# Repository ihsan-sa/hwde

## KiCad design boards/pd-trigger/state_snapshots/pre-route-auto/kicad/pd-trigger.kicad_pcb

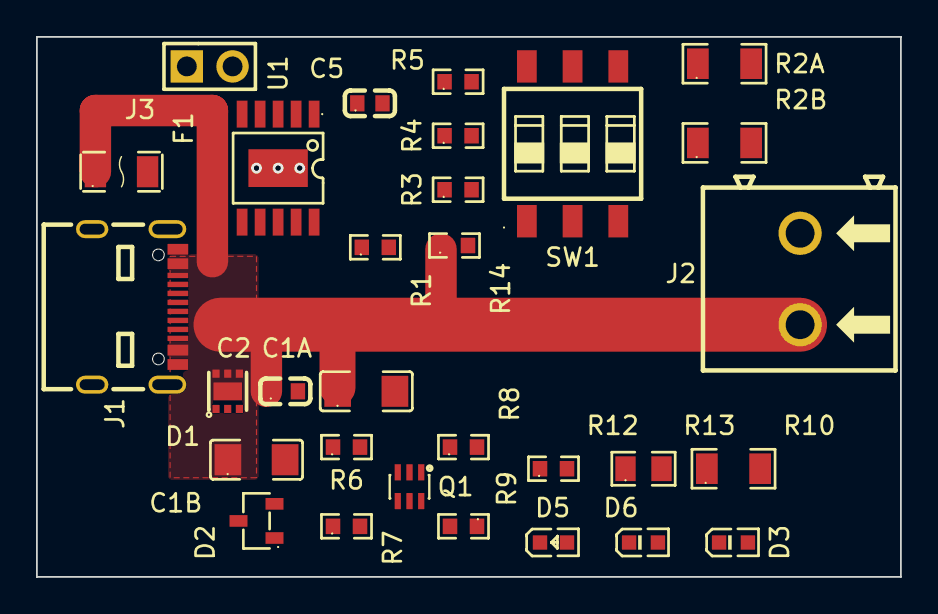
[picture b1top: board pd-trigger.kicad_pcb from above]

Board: 2 copper layers, 48.0 x 30.0 mm, 30 parts (0 on the bottom side), 21 nets.

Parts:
C1A, C1B: 10uF 50V X5R; C1206
C2: 100nF 50V X7R; C0603
C5: 1uF 50V X5R; C0603
D1: TVS2200 22V; WSON-6_L2.0-W2.0-P0.65-BL-EP
D2: BZX84C6V2; SOT-23-3_L2.9-W1.3-P1.90-LS2.4-BR
D3: LED YG PWR; LED0603-RD_GREEN
D5: LED RED 5V ONLY; LED0603-RD
D6: LED YG PROFILE OK; LED0603-RD_GREEN
F1: PPTC 1A 30V; F1206
J1: USB-C 16P 5A; USB-C-SMD_MC-311D
J2: SCREW 5.08 2P; CONN-TH_P5.08_KF128-5.08-2P
J3: HDR 1x2 AUX; HDR-TH_2P-P2.54-V-M-3
Q1: BC847BS; SOT-363-6_L2.2-W1.3-P0.65-LS2.1-BL
R1, R8: 10k; R0603
R2A, R2B: 510R; R1206
R3, R4, R5: 100k; R0603
R6: 6.8k; R0603
R7: 4.7k; R0603
R9: 47k; R0603
R10: 3.3k; R1206
R12: 1.5k; R0603
R13: 4.7k; R0805
R14: 0R; R0603
SW1: DIP-3; SW-SMD_6P-L7.6-W6.0-P2.54-LS9.3-BL
U1: CH224K; ESSOP-10_L4.9-W3.9-P1.0-LS6.0-TL-EP

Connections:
/BC12_DIS: U1.4, U1.5
/CC1: J1.A5, U1.7
/CC2: J1.B5, U1.6
/CFG1: R3.2, SW1.1, U1.9
/CFG2: R4.2, SW1.2, U1.2
/CFG3: R5.2, SW1.3, U1.3
/D3_A: D3.2, R10.2
/D5_A: D5.2, R12.2
/D6_A: D6.2, R13.2
/FB_B: Q1.5, R9.2
/FB_K: D5.1, Q1.3
/HV_B: Q1.2, R6.2, R7.1
/HV_OK: D6.1, Q1.6, R8.2, R9.1
/R2_MID: R2A.2, R2B.1
/VAUX: F1.2, J3.1
/VDD: C5.1, R2B.2, R3.1, R4.1, R5.1, U1.1
/VIND: D2.3, R1.1, R2A.1, R8.1, R10.1, R12.1, R13.1, R14.2
/VSENSE: R1.2, U1.8
/ZBIAS: D2.1, R6.1
GND: C1A.2, C1B.2, C2.2, C5.2, D1.1, D1.2, D1.3, D1.7, D3.1, J1.1, J1.2, J1.3, J1.4, J1.A1-B12, J1.B1-A12, J2.2, J3.2, Q1.1, Q1.4, R7.2, SW1.4, SW1.5, SW1.6, U1.11
VBUS: C1A.1, C1B.1, C2.1, D1.4, D1.5, D1.6, F1.1, J1.A4-B9, J1.B4-A9, J2.1, R14.1

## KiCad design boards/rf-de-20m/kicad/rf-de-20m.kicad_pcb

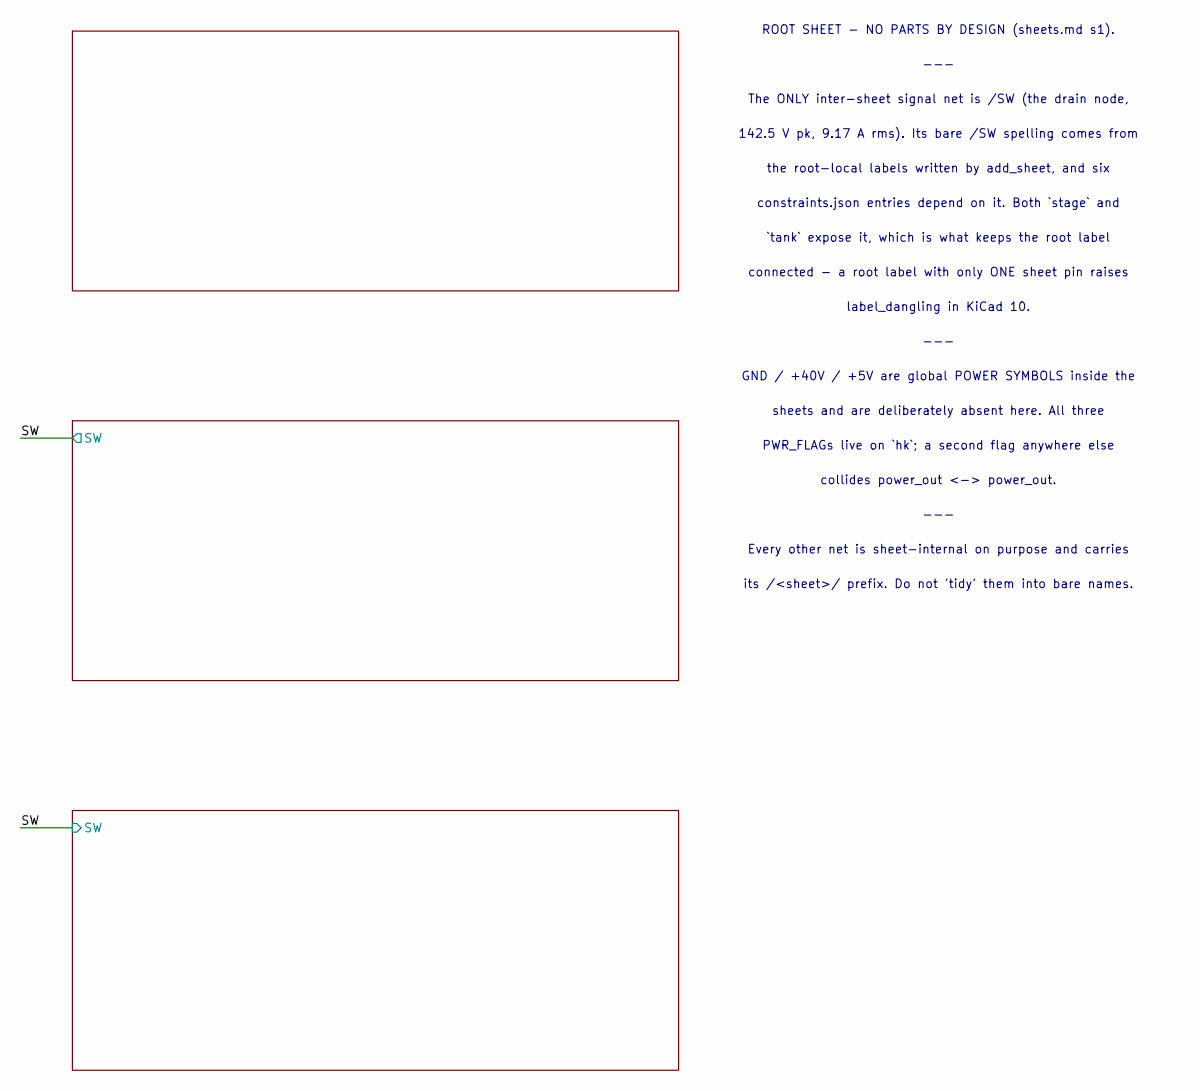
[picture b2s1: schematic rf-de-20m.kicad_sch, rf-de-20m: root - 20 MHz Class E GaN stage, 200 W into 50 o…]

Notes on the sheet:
ROOT SHEET - NO PARTS BY DESIGN (sheets.md s1).
---
The ONLY inter-sheet signal net is /SW (the drain node,
142.5 V pk, 9.17 A rms). Its bare /SW spelling comes from
the root-local labels written by add_sheet, and six
constraints.json entries depend on it. Both `stage` and
`tank` expose it, which is what keeps the root label
connected - a root label with only ONE sheet pin raises
label_dangling in KiCad 10.
GND / +40V / +5V are global POWER SYMBOLS inside the
sheets and are deliberately absent here. All three
PWR_FLAGs live on `hk`; a second flag anywhere else
collides power_out <-> power_out.
Every other net is sheet-internal on purpose and carries
its /<sheet>/ prefix. Do not 'tidy' them into bare names.

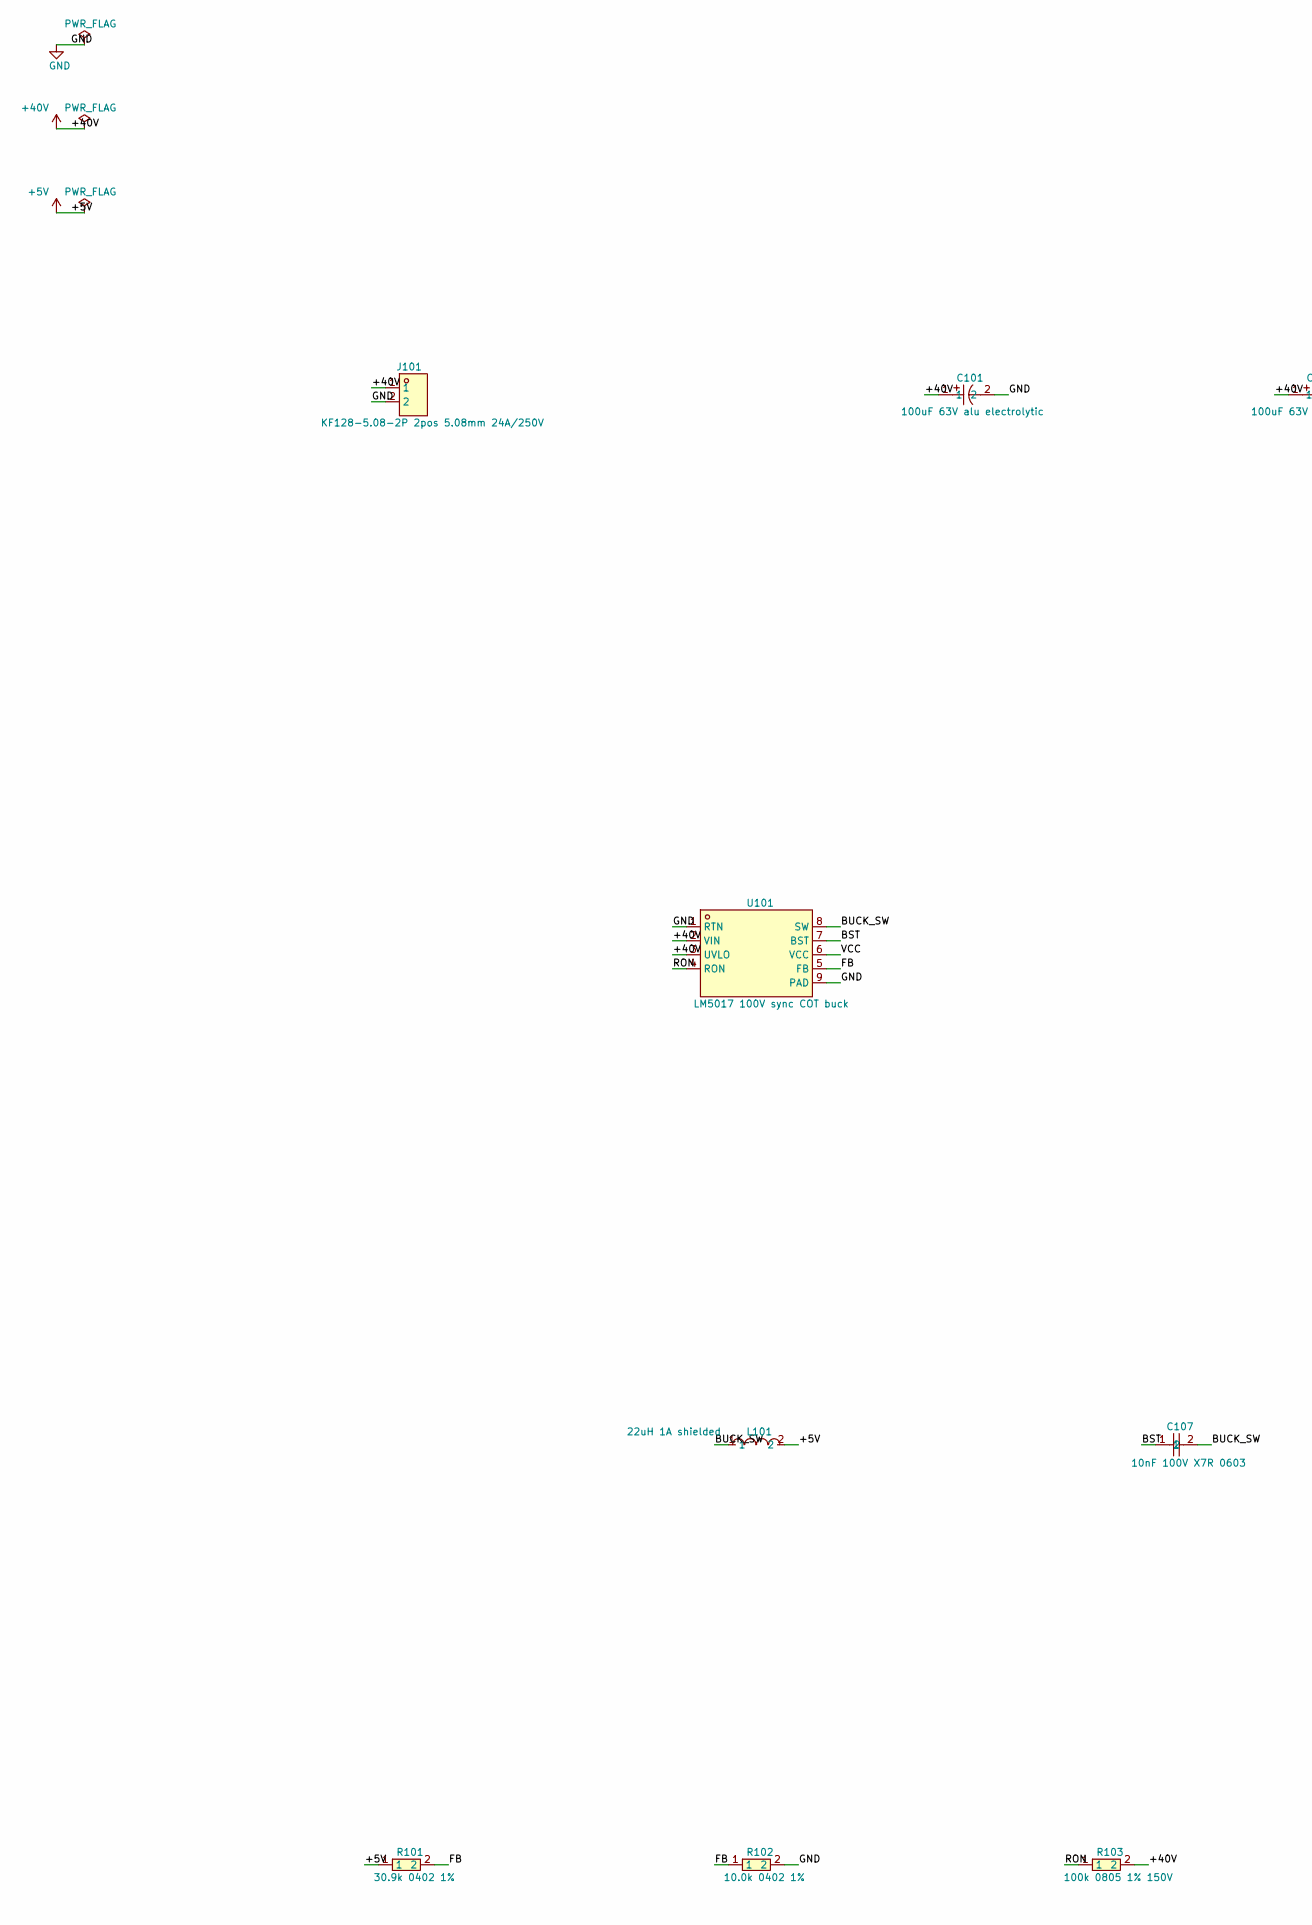
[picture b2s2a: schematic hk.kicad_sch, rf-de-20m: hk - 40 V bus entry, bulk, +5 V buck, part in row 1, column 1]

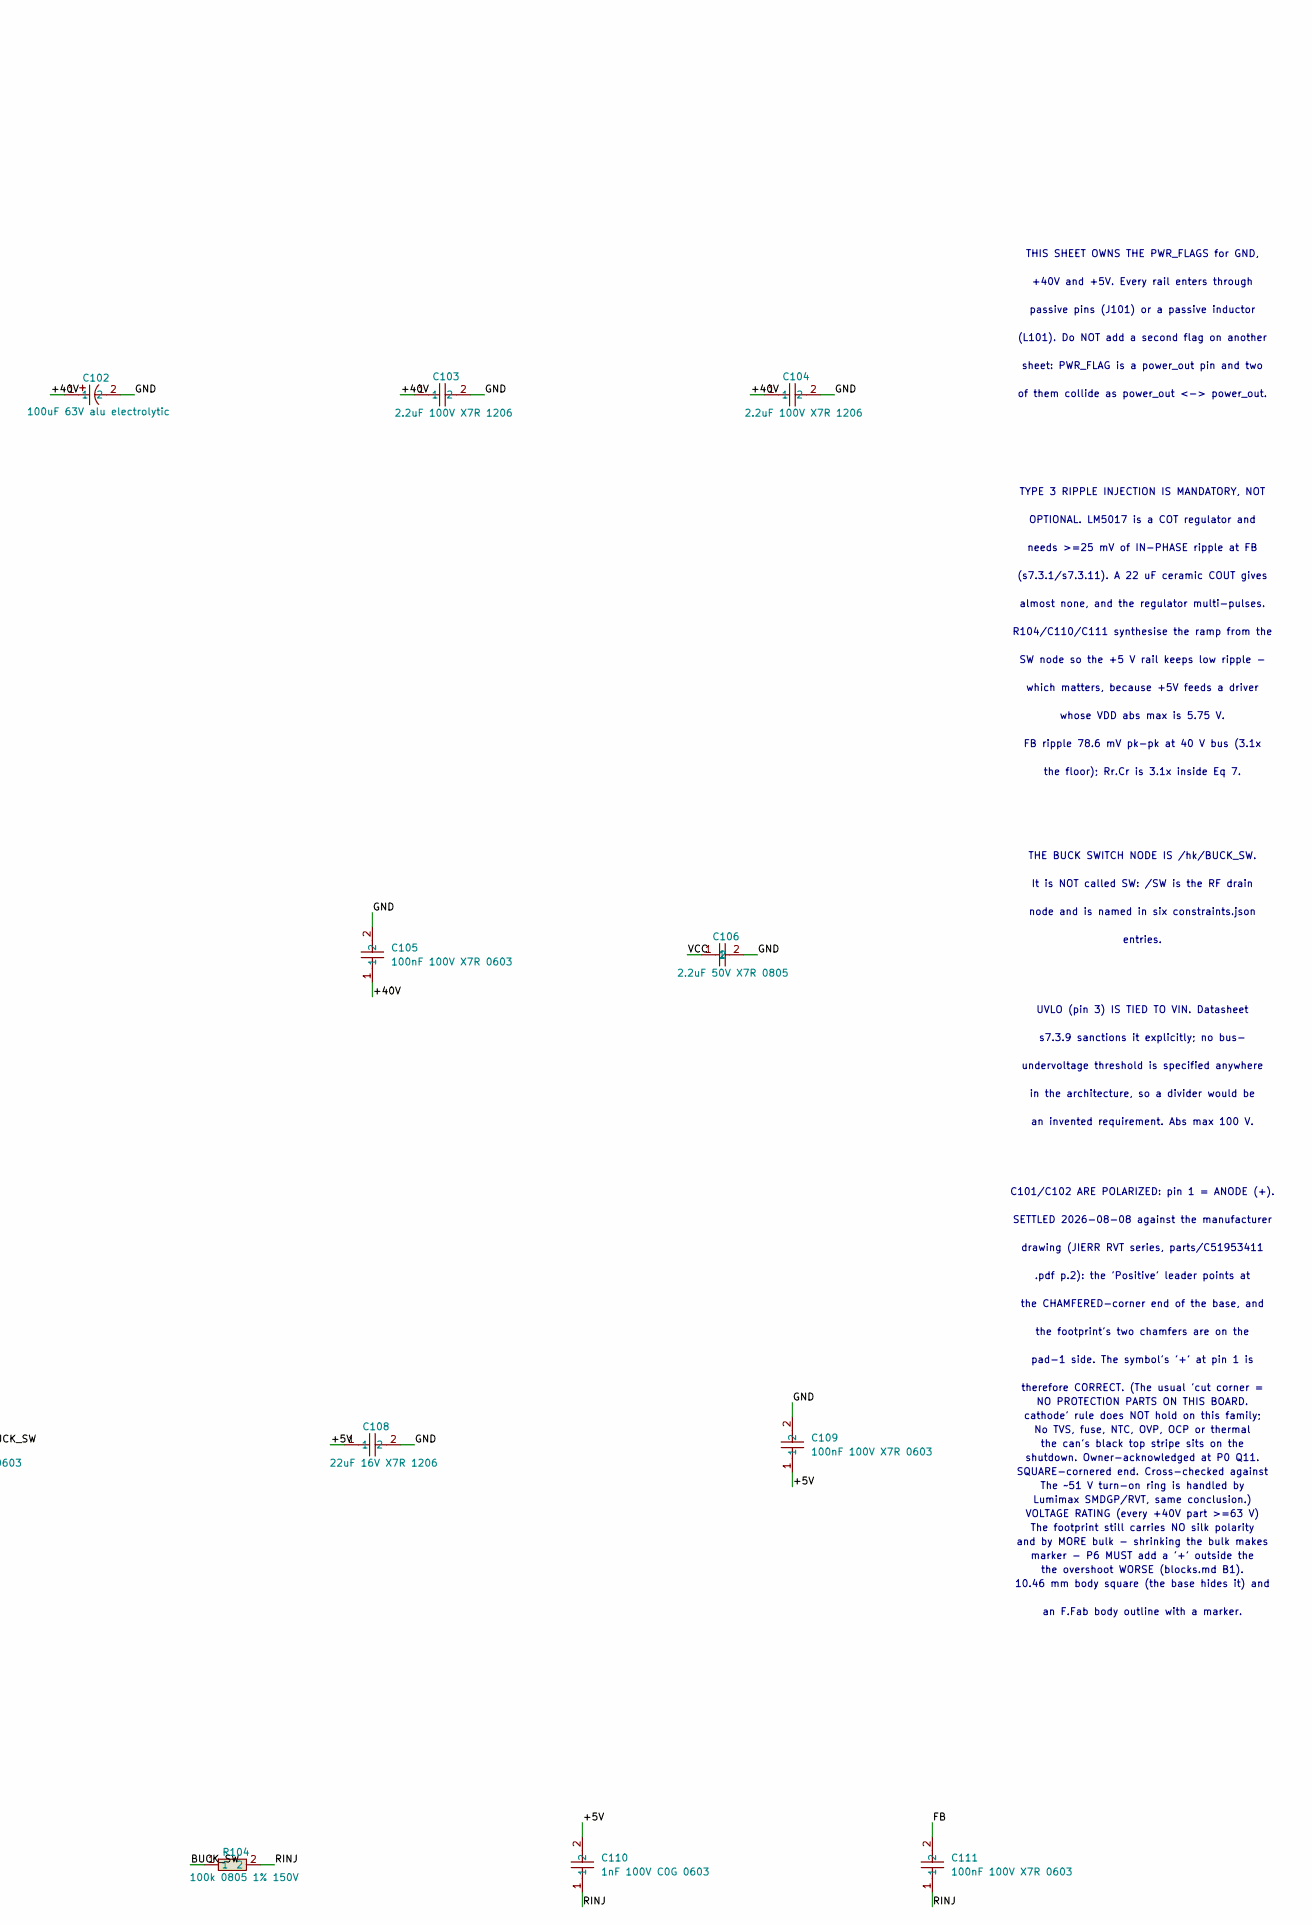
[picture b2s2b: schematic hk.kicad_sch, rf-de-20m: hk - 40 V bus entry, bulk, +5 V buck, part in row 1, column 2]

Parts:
C101, C102: 100uF 63V alu electrolytic; CAP-SMD_BD10.0-L10.3-W10.3-LS11.0-FD_1; LCSC C51953411
C103, C104: 2.2uF 100V X7R 1206; C1206; LCSC C577211
C105, C109, C111: 100nF 100V X7R 0603; C0603; LCSC C113803
C106: 2.2uF 50V X7R 0805; C0805; LCSC C125847
C107: 10nF 100V X7R 0603; C0603; LCSC C107059
C108: 22uF 16V X7R 1206; C1206; LCSC C22392398
C110: 1nF 100V C0G 0603; C0603; LCSC C113793
J101: KF128-5.08-2P 2pos 5.08mm 24A/250V; CONN-TH_P5.08_KF128-5.08-2P_EDGETRIM; LCSC C474952
L101: 22uH 1A shielded; IND-SMD_L4.0-W4.0_SLW4010S; LCSC C83472
R101: 30.9k 0402 1%; R0402; LCSC C270615
R102: 10.0k 0402 1%; R0402; LCSC C25744
R103, R104: 100k 0805 1% 150V; R0805; LCSC C149504
U101: LM5017 100V sync COT buck; SOIC-8-EP_LM5017_TI-MRA08B; LCSC C34355

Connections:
+5V: C108.1, C109.1, C110.2, L101.2, R101.1; also elsewhere on the board
+40V: C101.1, C102.1, C103.1, C104.1, C105.1, J101.1, R103.2, U101.2 (VIN), U101.3 (UVLO); also elsewhere on the board
/hk/BST: C107.1, U101.7 (BST)
/hk/BUCK_SW: C107.2, L101.1, R104.1, U101.8 (SW)
/hk/FB: C111.2, R101.2, R102.1, U101.5 (FB)
/hk/RINJ: C110.1, C111.1, R104.2
/hk/RON: R103.1, U101.4 (RON)
/hk/VCC: C106.1, U101.6 (VCC)
GND: C101.2, C102.2, C103.2, C104.2, C105.2, C106.2, C108.2, C109.2, J101.2, R102.2, U101.1 (RTN), U101.9 (PAD); also elsewhere on the board

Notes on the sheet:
THIS SHEET OWNS THE PWR_FLAGS for GND,
+40V and +5V. Every rail enters through
passive pins (J101) or a passive inductor
(L101). Do NOT add a second flag on another
sheet: PWR_FLAG is a power_out pin and two
of them collide as power_out <-> power_out.
TYPE 3 RIPPLE INJECTION IS MANDATORY, NOT
OPTIONAL. LM5017 is a COT regulator and
needs >=25 mV of IN-PHASE ripple at FB
(s7.3.1/s7.3.11). A 22 uF ceramic COUT gives
almost none, and the regulator multi-pulses.
R104/C110/C111 synthesise the ramp from the
SW node so the +5 V rail keeps low ripple -
which matters, because +5V feeds a driver
whose VDD abs max is 5.75 V.
FB ripple 78.6 mV pk-pk at 40 V bus (3.1x
the floor); Rr.Cr is 3.1x inside Eq 7.
THE BUCK SWITCH NODE IS /hk/BUCK_SW.
It is NOT called SW: /SW is the RF drain
node and is named in six constraints.json
entries.
UVLO (pin 3) IS TIED TO VIN. Datasheet
s7.3.9 sanctions it explicitly; no bus-
undervoltage threshold is specified anywhere
in the architecture, so a divider would be
an invented requirement. Abs max 100 V.
C101/C102 ARE POLARIZED: pin 1 = ANODE (+).
SETTLED 2026-08-08 against the manufacturer
drawing (JIERR RVT series, parts/C51953411
.pdf p.2): the 'Positive' leader points at
the CHAMFERED-corner end of the base, and
the footprint's two chamfers are on the
pad-1 side. The symbol's '+' at pin 1 is
therefore CORRECT. (The usual 'cut corner =
cathode' rule does NOT hold on this family;
the can's black top stripe sits on the
SQUARE-cornered end. Cross-checked against
Lumimax SMDGP/RVT, same conclusion.)
The footprint still carries NO silk polarity
marker - P6 MUST add a '+' outside the

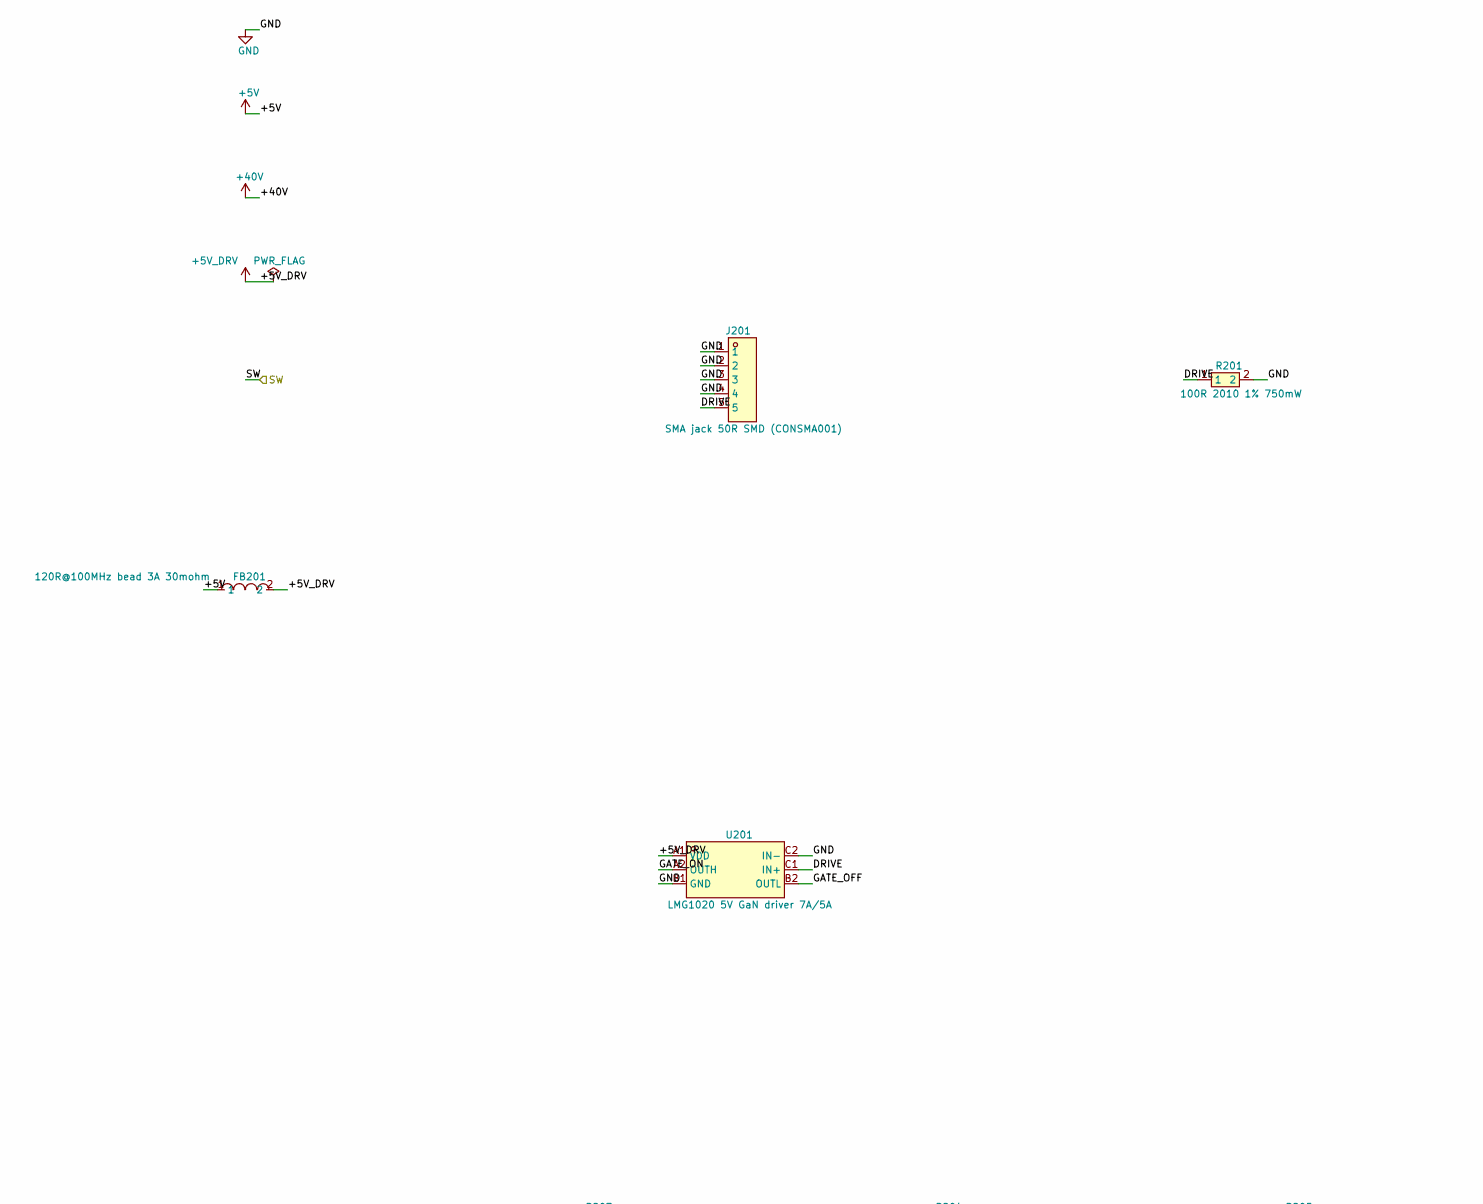
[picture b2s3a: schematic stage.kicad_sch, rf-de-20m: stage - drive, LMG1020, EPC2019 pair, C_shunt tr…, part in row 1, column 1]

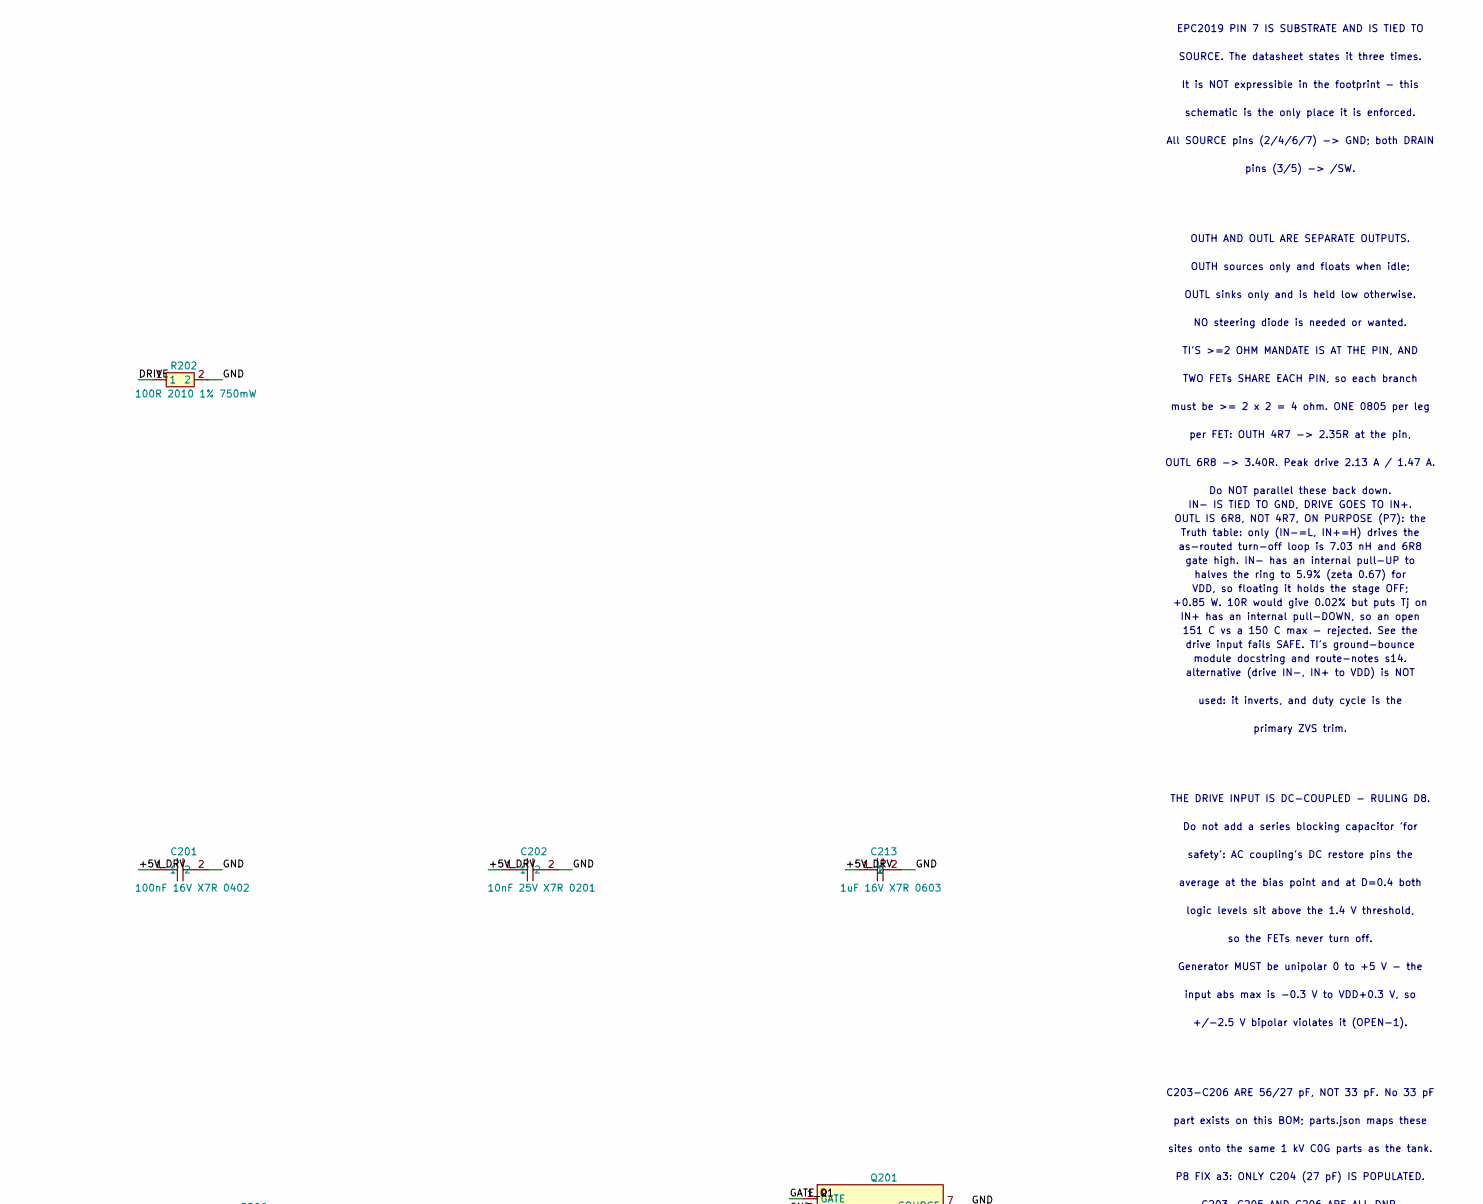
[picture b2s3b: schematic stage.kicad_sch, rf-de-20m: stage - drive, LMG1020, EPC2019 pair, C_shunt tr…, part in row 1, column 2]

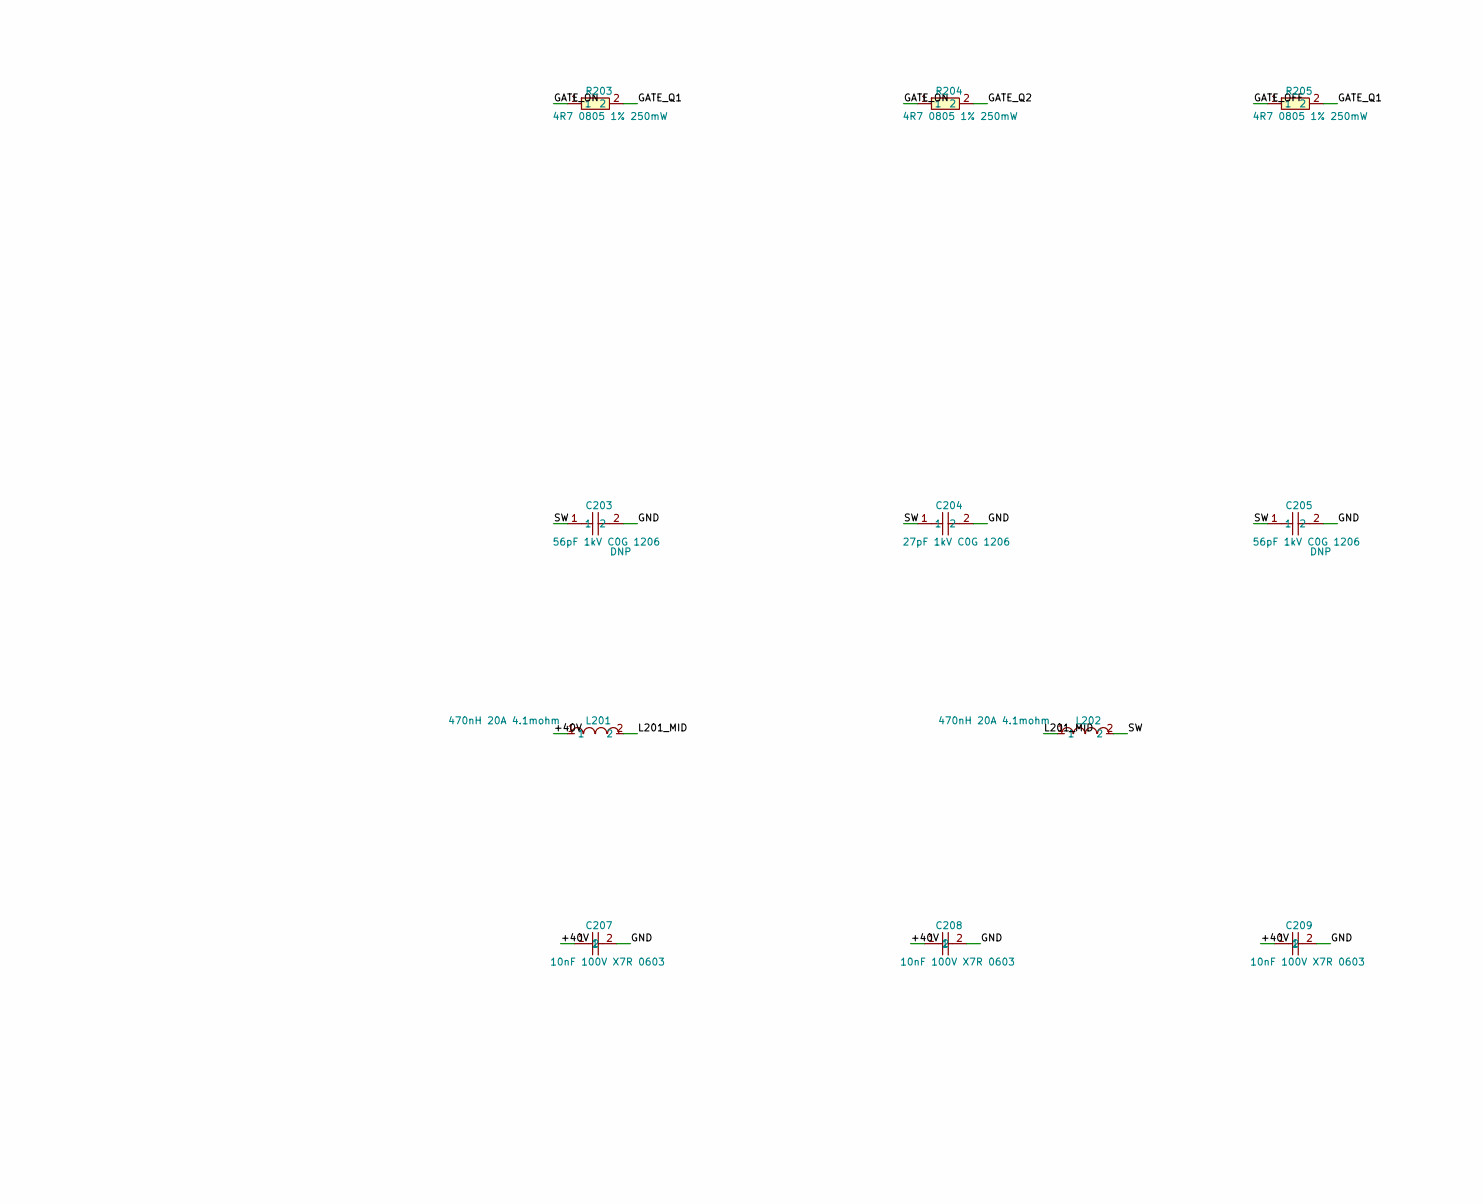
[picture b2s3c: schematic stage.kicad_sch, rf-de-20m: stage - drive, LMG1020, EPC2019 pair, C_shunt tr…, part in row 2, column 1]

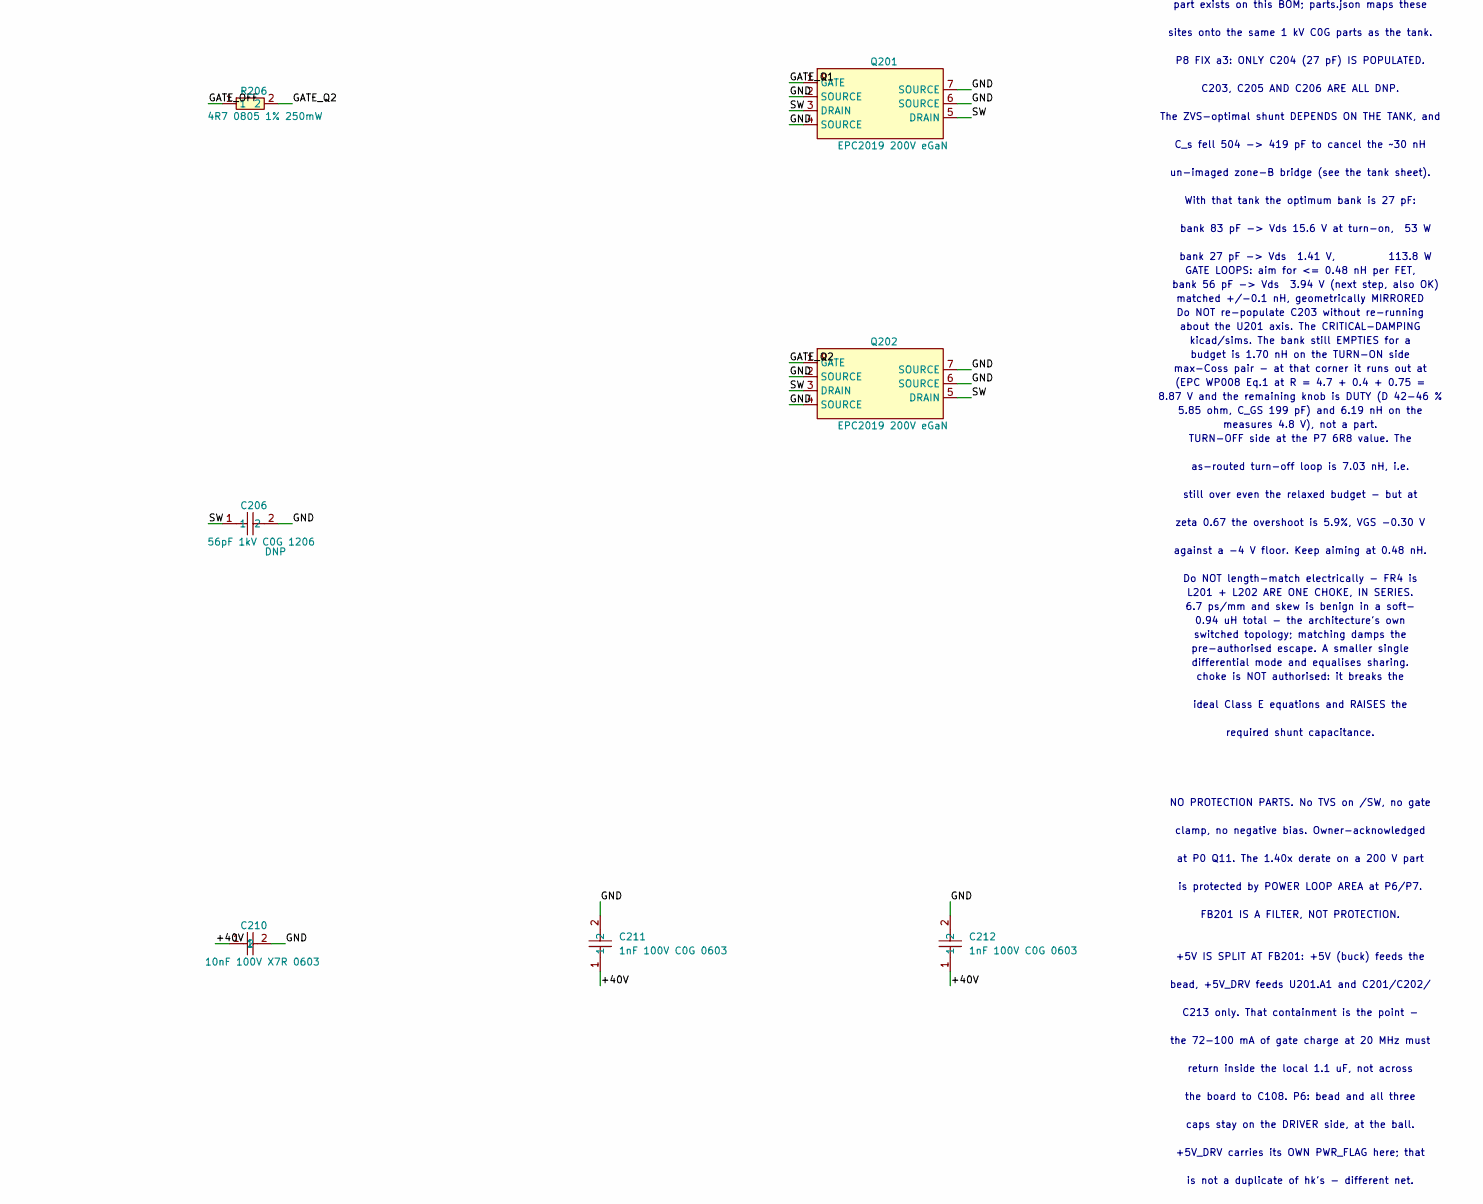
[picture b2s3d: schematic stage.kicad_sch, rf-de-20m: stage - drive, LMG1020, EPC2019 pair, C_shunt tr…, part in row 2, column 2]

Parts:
C201: 100nF 16V X7R 0402; C0402; LCSC C60474
C202: 10nF 25V X7R 0201; C0201; LCSC C285010
C203, C205, C206: 56pF 1kV C0G 1206; C1206; LCSC C113875
C204: 27pF 1kV C0G 1206; C1206; LCSC C541492
C207, C208, C209, C210: 10nF 100V X7R 0603; C0603; LCSC C107059
C211, C212: 1nF 100V C0G 0603; C0603; LCSC C113793
C213: 1uF 16V X7R 0603; C0603; LCSC C106248
FB201: 120R@100MHz bead 3A 30mohm; L0805; LCSC C79382
J201: SMA jack 50R SMD (CONSMA001); SMA-SMD_CONSMA001-SMD-G-T; LCSC C22418168
L201, L202: 470nH 20A 4.1mohm; IND-SMD_L7.0-W6.6_FXL0630; LCSC C167212
Q201, Q202: EPC2019 200V eGaN; TRS-SMD_EPC2019; LCSC C2836675
R201, R202: 100R 2010 1% 750mW; R2010; LCSC C421954
R203, R204, R205, R206: 4R7 0805 1% 250mW; R0805; LCSC C160081
U201: LMG1020 5V GaN driver 7A/5A; BGA-6_L1.3-W0.8-P0.40-TL_PTMAG3001A2YBGR; LCSC C6423790

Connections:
+5V: FB201.1; also elsewhere on the board
+5V_DRV: C201.1, C202.1, C213.1, FB201.2, U201.A1 (VDD)
+40V: C207.1, C208.1, C209.1, C210.1, C211.1, C212.1, L201.1; also elsewhere on the board
/SW: C203.1, C204.1, C205.1, C206.1, L202.2, Q201.3 (DRAIN), Q201.5 (DRAIN), Q202.3 (DRAIN), Q202.5 (DRAIN); also elsewhere on the board
/stage/DRIVE: J201.5, R201.1, R202.1, U201.C1 (IN+)
/stage/GATE_OFF: R205.1, R206.1, U201.B2 (OUTL)
/stage/GATE_ON: R203.1, R204.1, U201.A2 (OUTH)
/stage/GATE_Q1: Q201.1 (GATE), R203.2, R205.2
/stage/GATE_Q2: Q202.1 (GATE), R204.2, R206.2
/stage/L201_MID: L201.2, L202.1
GND: C201.2, C202.2, C203.2, C204.2, C205.2, C206.2, C207.2, C208.2, C209.2, C210.2, C211.2, C212.2, C213.2, J201.1, J201.2, J201.3, J201.4, Q201.2 (SOURCE), Q201.4 (SOURCE), Q201.6 (SOURCE), Q201.7 (SOURCE), Q202.2 (SOURCE), Q202.4 (SOURCE), Q202.6 (SOURCE), Q202.7 (SOURCE), R201.2, R202.2, U201.B1 (GND), U201.C2 (IN-); also elsewhere on the board

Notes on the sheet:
EPC2019 PIN 7 IS SUBSTRATE AND IS TIED TO
SOURCE. The datasheet states it three times.
It is NOT expressible in the footprint - this
schematic is the only place it is enforced.
All SOURCE pins (2/4/6/7) -> GND; both DRAIN
pins (3/5) -> /SW.
OUTH AND OUTL ARE SEPARATE OUTPUTS.
OUTH sources only and floats when idle;
OUTL sinks only and is held low otherwise.
NO steering diode is needed or wanted.
TI'S >=2 OHM MANDATE IS AT THE PIN, AND
TWO FETs SHARE EACH PIN, so each branch
must be >= 2 x 2 = 4 ohm. ONE 0805 per leg
per FET: OUTH 4R7 -> 2.35R at the pin,
OUTL 6R8 -> 3.40R. Peak drive 2.13 A / 1.47 A.
Do NOT parallel these back down.
OUTL IS 6R8, NOT 4R7, ON PURPOSE (P7): the
as-routed turn-off loop is 7.03 nH and 6R8
halves the ring to 5.9% (zeta 0.67) for
+0.85 W. 10R would give 0.02% but puts Tj on
151 C vs a 150 C max - rejected. See the
module docstring and route-notes s14.
IN- IS TIED TO GND, DRIVE GOES TO IN+.
Truth table: only (IN-=L, IN+=H) drives the
gate high. IN- has an internal pull-UP to
VDD, so floating it holds the stage OFF;
IN+ has an internal pull-DOWN, so an open
drive input fails SAFE. TI's ground-bounce
alternative (drive IN-, IN+ to VDD) is NOT
used: it inverts, and duty cycle is the
primary ZVS trim.
THE DRIVE INPUT IS DC-COUPLED - RULING D8.
Do not add a series blocking capacitor 'for
safety': AC coupling's DC restore pins the
average at the bias point and at D=0.4 both
logic levels sit above the 1.4 V threshold,
so the FETs never turn off.
Generator MUST be unipolar 0 to +5 V - the
input abs max is -0.3 V to VDD+0.3 V, so
+/-2.5 V bipolar violates it (OPEN-1).
